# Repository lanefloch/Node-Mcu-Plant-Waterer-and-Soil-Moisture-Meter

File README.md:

# Node-Mcu-Plant-Waterer-and-Soil-Moisture-Meter
Node Mcu powered plant waterer using custom PCB

Fusion 360 link - https://a360.co/2vmXInX

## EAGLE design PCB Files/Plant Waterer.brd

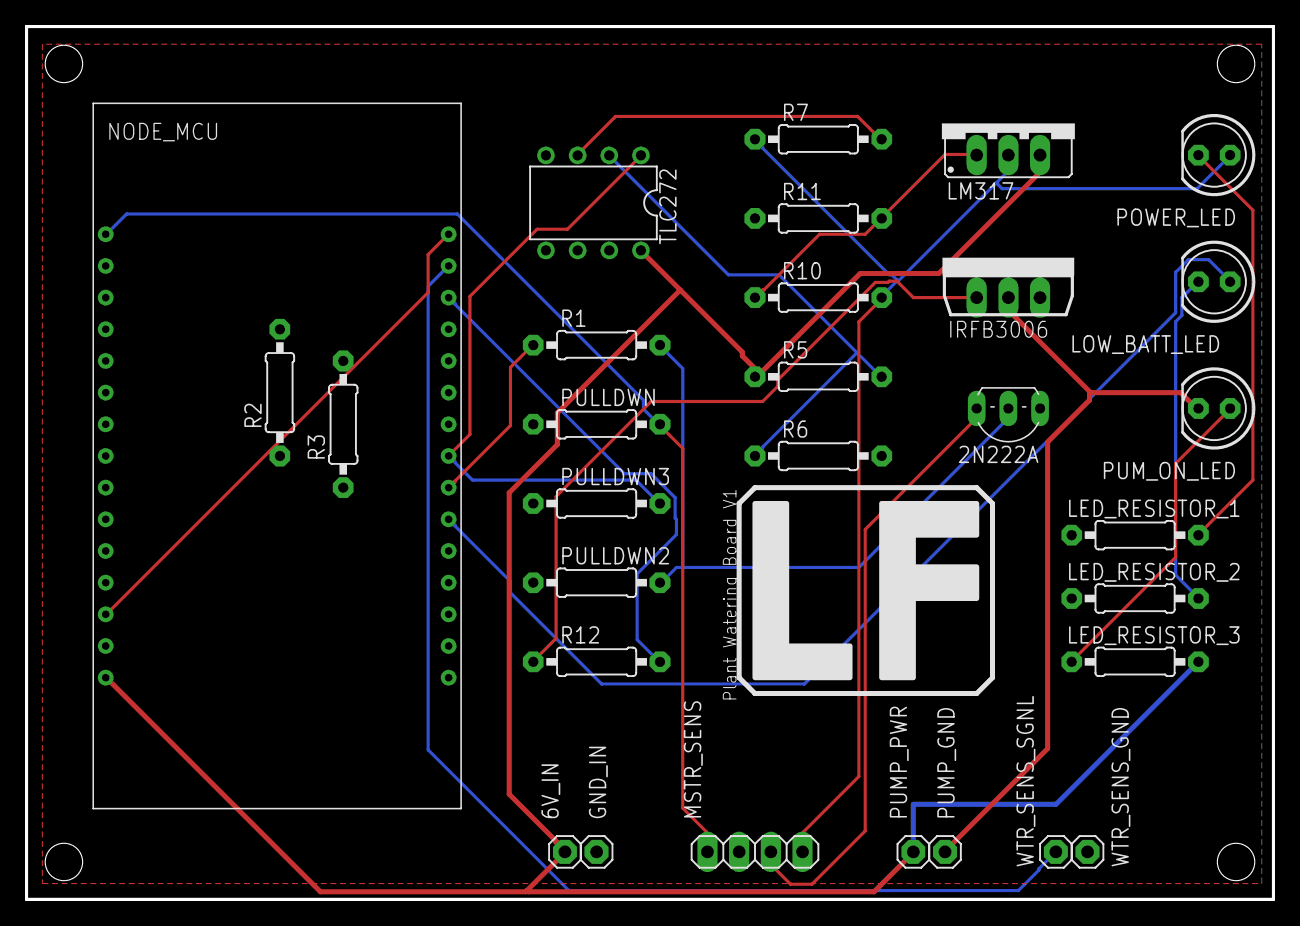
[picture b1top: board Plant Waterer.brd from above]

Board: 2 copper layers, 100.0 x 70.0 mm, 30 parts (0 on the bottom side), 23 nets.

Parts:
2N222A: 2N2222; TO92-EBC-OVAL
6V_IN: 1X01
GND_IN: 1X01
IRFB3006: IRFB3006; TO262-V
LED_RESISTOR_1, LED_RESISTOR_2, LED_RESISTOR_3: 2.2k; 0207/10
LM317: 317TS
LOW_BATT_LED: LED5MM
MSTR_SENS: 1X04
NODE_MCU: NODEMCU_V3
POWER_LED: LED5MM
PULLDWN, PULLDWN2, PULLDWN3: 10k; 0207/10
PUMP_GND: 1X01
PUMP_PWR: 1X01
PUM_ON_LED: LED5MM
R1, R12: 320; 0207/10
R2, R3: 4.7K; 0207/10
R5: 680; 0207/10
R6: 820; 0207/10
R7: 1k; 0207/10
R10: 220; 0207/10
R11: 330; 0207/10
TLC272: TLC272P; DIL08
WTR_SENS_GND: 1X01
WTR_SENS_SGNL: 1X01

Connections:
3.3_INTO_COMPARATOR: R7.2, TLC272.3
3.3_REG: LM317.2, MSTR_SENS.4, POWER_LED.A, R7.1, R10.2
A0: MSTR_SENS.1, NODE_MCU.A0, PULLDWN.2
D0: NODE_MCU.D0, NODE_MCU.RST
D1: NODE_MCU.D1, WTR_SENS_SGNL.1
D2: NODE_MCU.D2, R12.2
D5: NODE_MCU.D5, PULLDWN3.2, TLC272.1
D6: NODE_MCU.D6, R1.1
D7: LOW_BATT_LED.A, NODE_MCU.D7
GND: 2N222A.E, GND_IN.1, IRFB3006.3, LED_RESISTOR_1.1, LED_RESISTOR_2.1, NODE_MCU.GND, PULLDWN.1, PULLDWN2.1, PULLDWN3.1, R6.2, R11.1, TLC272.4, WTR_SENS_GND.1
LED_PWR: LED_RESISTOR_1.2, POWER_LED.K
LED_PWR2: LED_RESISTOR_2.2, LOW_BATT_LED.K
LED_PWR3: LED_RESISTOR_3.1, PUM_ON_LED.A
LM317_ADJ: LM317.1, R10.1, R11.2
MOSFET_GATE: IRFB3006.1, R12.1
unnamed: NODE_MCU.D3, R2.2
unnamed: NODE_MCU.D4, R3.2
unnamed: NODE_MCU.3V3, R2.1, R3.1
PMP_GRD: IRFB3006.2, PUMP_GND.1, PUM_ON_LED.K
PWR_TO_MSTR_SENS: 2N222A.C, MSTR_SENS.3
SIGNL_INTO_2N222A: 2N222A.B, PULLDWN2.2, R1.2
VIN: 6V_IN.1, LED_RESISTOR_3.2, LM317.3, NODE_MCU.VIN, PUMP_PWR.1, R5.1, TLC272.8
VLTG_DIV_INTO_COMPARATOR: R5.2, R6.1, TLC272.2

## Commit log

2020-01-26 Uploaded EAGLE board and schematic files
2020-01-27 Fixed #2, added some more debug prints, general improvements
2020-01-27 added low batt alert
    Made it so when the battery is low, instead of going to sleep it just shuts off the wifi to save a bit of power and continuously blinks the Low batt led
2020-01-27 Spelling Mistakes
2020-02-12 Removed delays and various improvements
2020-02-12 probably working version
2020-02-17 tested and functional
2020-02-23 Various Improvments
2020-04-09 Re-added Tweeting
